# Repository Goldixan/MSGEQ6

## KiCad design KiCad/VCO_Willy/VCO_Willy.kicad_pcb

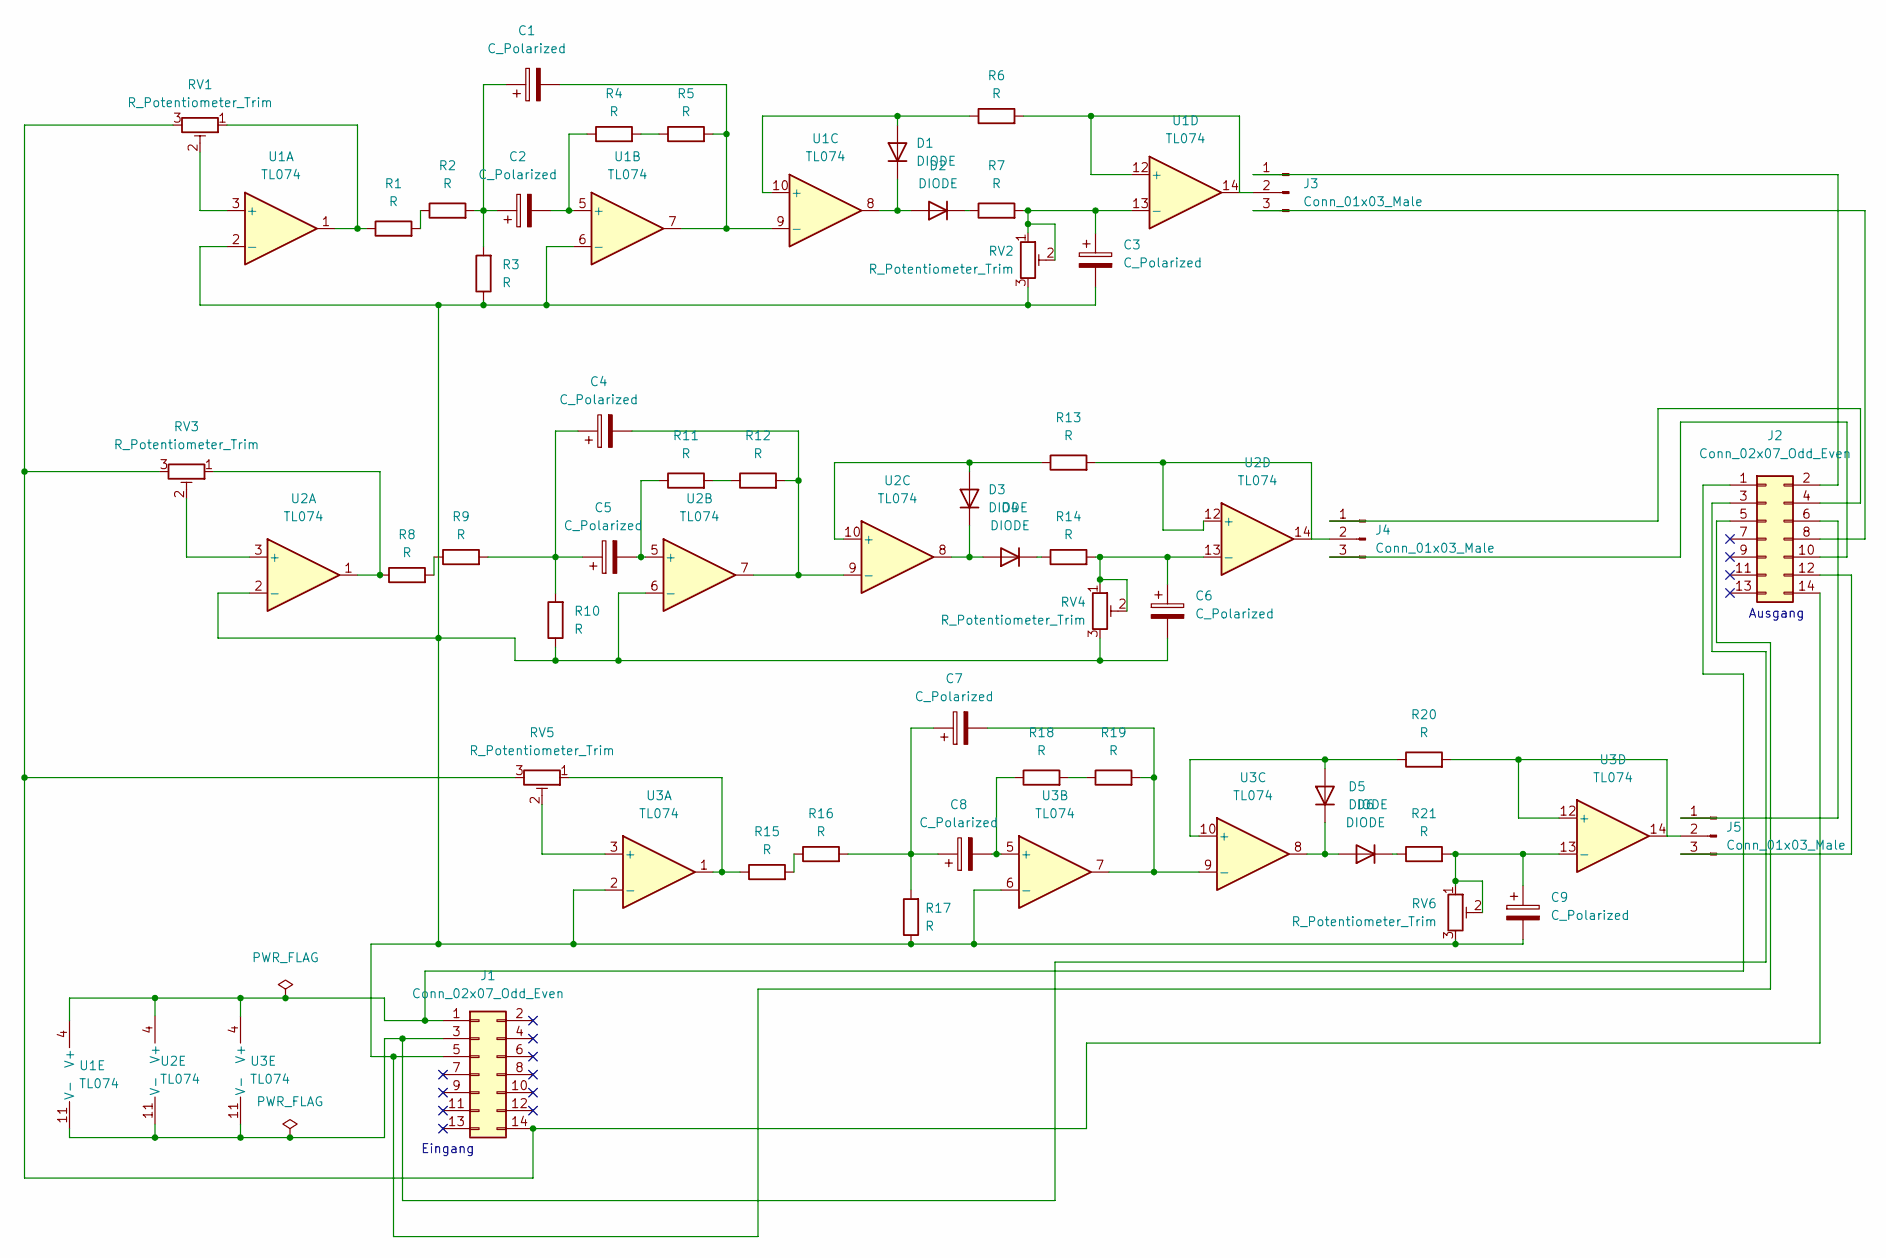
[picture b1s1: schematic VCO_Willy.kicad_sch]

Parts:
C1, C2, C3, C4, C5, C6, C7, C8, C9: C_Polarized; CP_Radial_Tantal_D4.5mm_P5.00mm
D1, D2, D3, D4, D5, D6: DIODE; D_DO-35_SOD27_P7.62mm_Horizontal
J1, J2: Conn_02x07_Odd_Even; IDC-Header_2x07_P2.54mm_Vertical
J3, J4, J5: Conn_01x03_Male; PinHeader_1x03_P2.54mm_Horizontal
R1, R2, R3, R4, R5, R6, R7, R8, R9, R10, R11, R12, R13, R14, R15, R16, R17, R18, R19, R20, R21: R; R_Axial_DIN0204_L3.6mm_D1.6mm_P7.62mm_Horizontal
RV1, RV2, RV3, RV4, RV5, RV6: R_Potentiometer_Trim; Potentiometer_Bourns_3296W_Vertical
U1, U2, U3: TL074; DIP-14_W7.62mm_Socket

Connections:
unnamed: C1.1, C2.1, R2.2, R3.2
unnamed: C1.2, R5.2, U1.7, U1.9 (-)
unnamed: C2.2, R4.1, U1.5 (+)
unnamed: C3.1, R7.2, RV2.1, RV2.2, U1.13 (-)
unnamed: C3.2, C6.2, C9.2, J1.5, J2.5, R3.1, R10.1, R17.1, RV2.3, RV4.3, RV6.3, U1.2 (-), U1.6 (-), U2.2 (-), U2.6 (-), U3.2 (-), U3.6 (-)
unnamed: C4.1, C5.1, R9.2, R10.2
unnamed: C4.2, R12.2, U2.7, U2.9 (-)
unnamed: C5.2, R11.1, U2.5 (+)
unnamed: C6.1, R14.2, RV4.1, RV4.2, U2.13 (-)
unnamed: C7.1, C8.1, R16.2, R17.2
unnamed: C7.2, R19.2, U3.7, U3.9 (-)
unnamed: C8.2, R18.1, U3.5 (+)
unnamed: C9.1, R21.2, RV6.1, RV6.2, U3.13 (-)
unnamed: D1.1 (A), R6.1, U1.10 (+)
unnamed: D1.2 (K), D2.1 (A), U1.8
unnamed: D2.2 (K), R7.1
unnamed: D3.1 (A), R13.1, U2.10 (+)
unnamed: D3.2 (K), D4.1 (A), U2.8
unnamed: D4.2 (K), R14.1
unnamed: D5.1 (A), R20.1, U3.10 (+)
unnamed: D5.2 (K), D6.1 (A), U3.8
unnamed: D6.2 (K), R21.1
unnamed: J1.1, J2.1, U1.4 (V+), U2.4 (V+), U3.4 (V+)
unnamed: J1.3, J2.3, U1.11 (V-), U2.11 (V-), U3.11 (V-)
unnamed: J1.14, J2.14, RV1.3, RV3.3, RV5.3
unnamed: J2.2, J3.1
unnamed: J2.4, J4.1
unnamed: J2.6, J5.1
unnamed: J2.8, J3.3
unnamed: J2.10, J4.3
unnamed: J2.12, J5.3
unnamed: J3.2, R6.2, U1.12 (+), U1.14
unnamed: J4.2, R13.2, U2.12 (+), U2.14
unnamed: J5.2, R20.2, U3.12 (+), U3.14
unnamed: R1.1, RV1.1, U1.1
unnamed: R1.2, R2.1
unnamed: R4.2, R5.1
unnamed: R8.1, RV3.1, U2.1
unnamed: R8.2, R9.1
unnamed: R11.2, R12.1
unnamed: R15.1, RV5.1, U3.1
unnamed: R15.2, R16.1
unnamed: R18.2, R19.1
unnamed: RV1.2, U1.3 (+)
unnamed: RV3.2, U2.3 (+)
unnamed: RV5.2, U3.3 (+)

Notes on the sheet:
Eingang
Ausgang

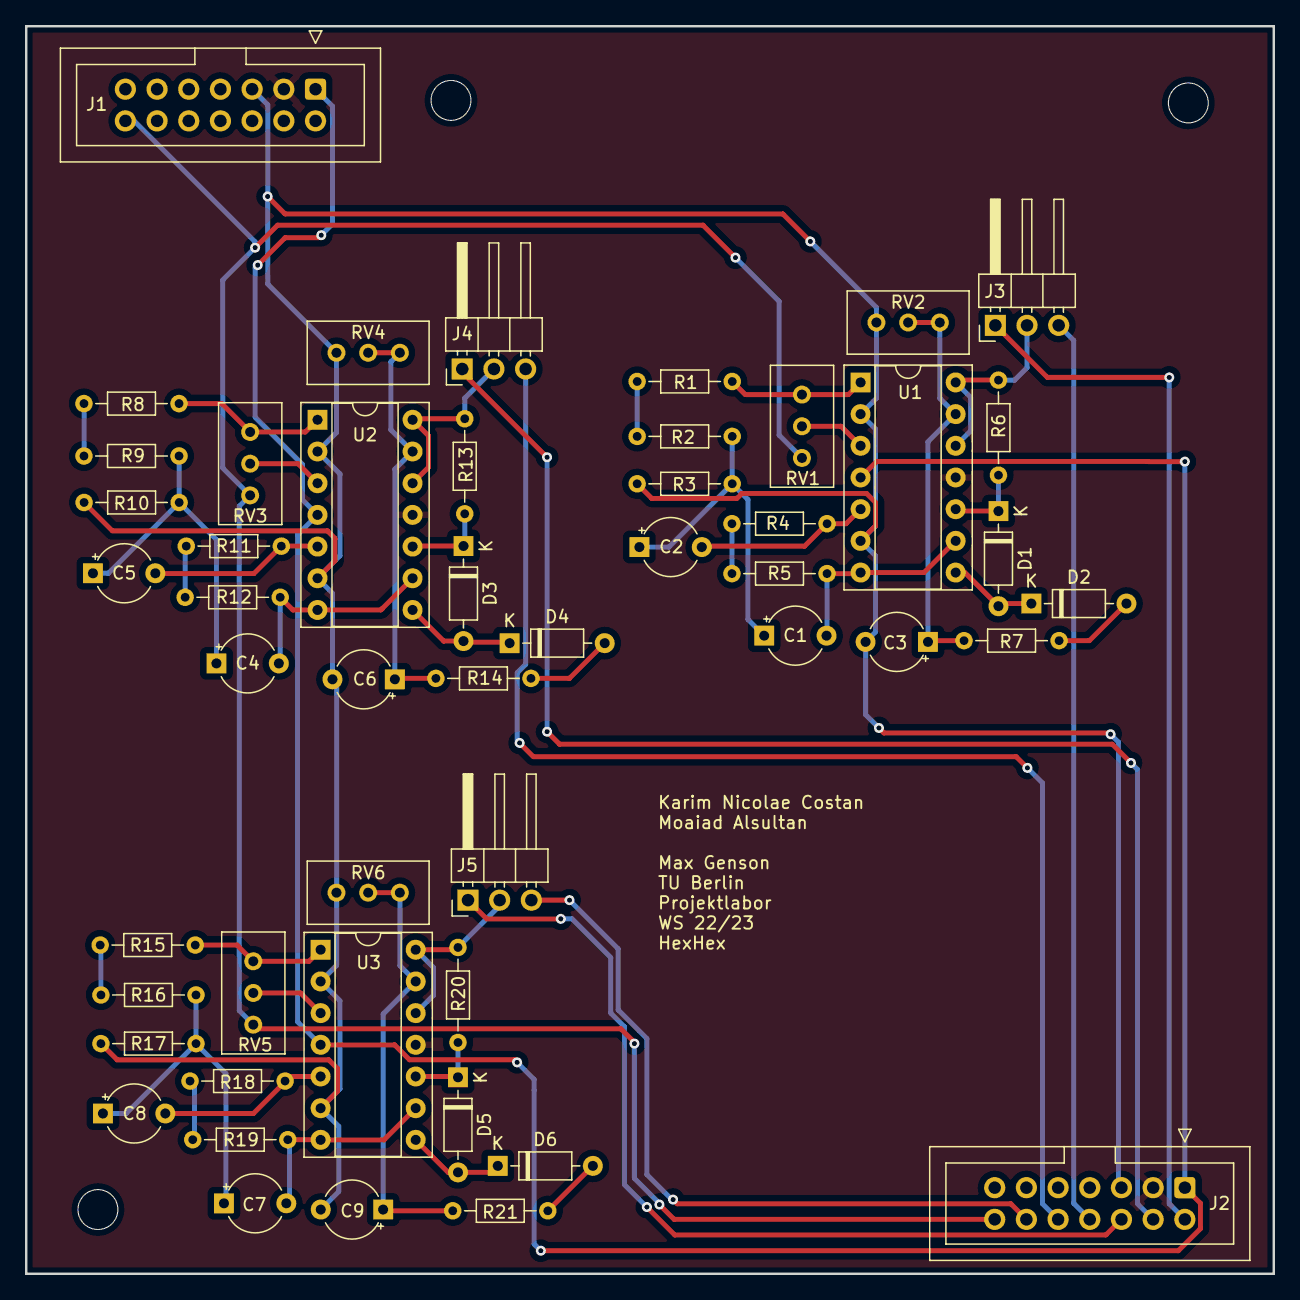
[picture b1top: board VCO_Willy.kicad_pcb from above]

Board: 2 copper layers, 100.0 x 100.0 mm, 50 parts (0 on the bottom side), 46 nets.

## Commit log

2022-11-18 Filter&PeakDetection implementiert
2022-11-18 Add files via upload
    correct the Peak dictator
2022-12-02 KiCad
2022-12-02 Dämpfer,Filter,Peak implementiert auf PCB
2022-12-02 finised the design of and on schema
2022-12-16 upload new design
